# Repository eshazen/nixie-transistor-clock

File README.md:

In 2013 I built a clock from a kit purchased here:  https://tube-clock.com/

* [Manual](neon_man.pdf)

* set_board - start of a design to set the time using an ESP32
* case - acrylic case design

Some circuit analysis for setting remotely.

Set switches (ref schematic in manual):

SW1 (minutes) - page 8/23 (PDF page 70)
SW2 (Hours) - page 10/23 (PDF page 72)
SW3 (s hold) - page 2/23 (PDF page 64)

### 2026-05-11

Based on Peter's claim that WWVB reception was ok at Deb's place,
purchased a [Canaduino Atomic Clock](https://www.canaduino.ca/downloads/CANADUINO_Atomic_Clock_Receiver_Kit_V4.pdf)
board and 3D printed a little holder for it.  It seems to work OK
powered by 2xAA batteries in the kitchen.  Maybe at night it will work
in a window?

Per suggestion in the datasheet, thinking to connect with a shielded
RJ-45 patch cable.  Re-do `set_board_avr` to accommodate the connector,
and remove the 8MHz crystal and WiFi module.

Should probably add a couple of buttons.

Also, maybe need an additional small PCB for the WWVB board
with jumpers for LED and power (choose between battery and remote power).

### 2026-04-29

Confirm that ESP-01 works using FTDI at 115200 baud.
<br>Problem is that hardware UART on 8MHz AVR is unreliable.
<br>Downloaded https://github.com/nerdralph/picoUART
<br>Tested on "control panel" PCB with FTDI and seems to work

Starting to write some WiFi test code

### 2026-04-23

Reviving the "set board" project.  Thinking of a new design with an
ESP-01 serial WiFi module connected to a small AVR (ATTiny85?).
This could be much lower power or even fire up once only on power-up
to retrieve the time from somewhere.

The main issue may be poor wifi in the kitchen!

ESP-01 doco at:  https://nurdspace.nl/ESP8266

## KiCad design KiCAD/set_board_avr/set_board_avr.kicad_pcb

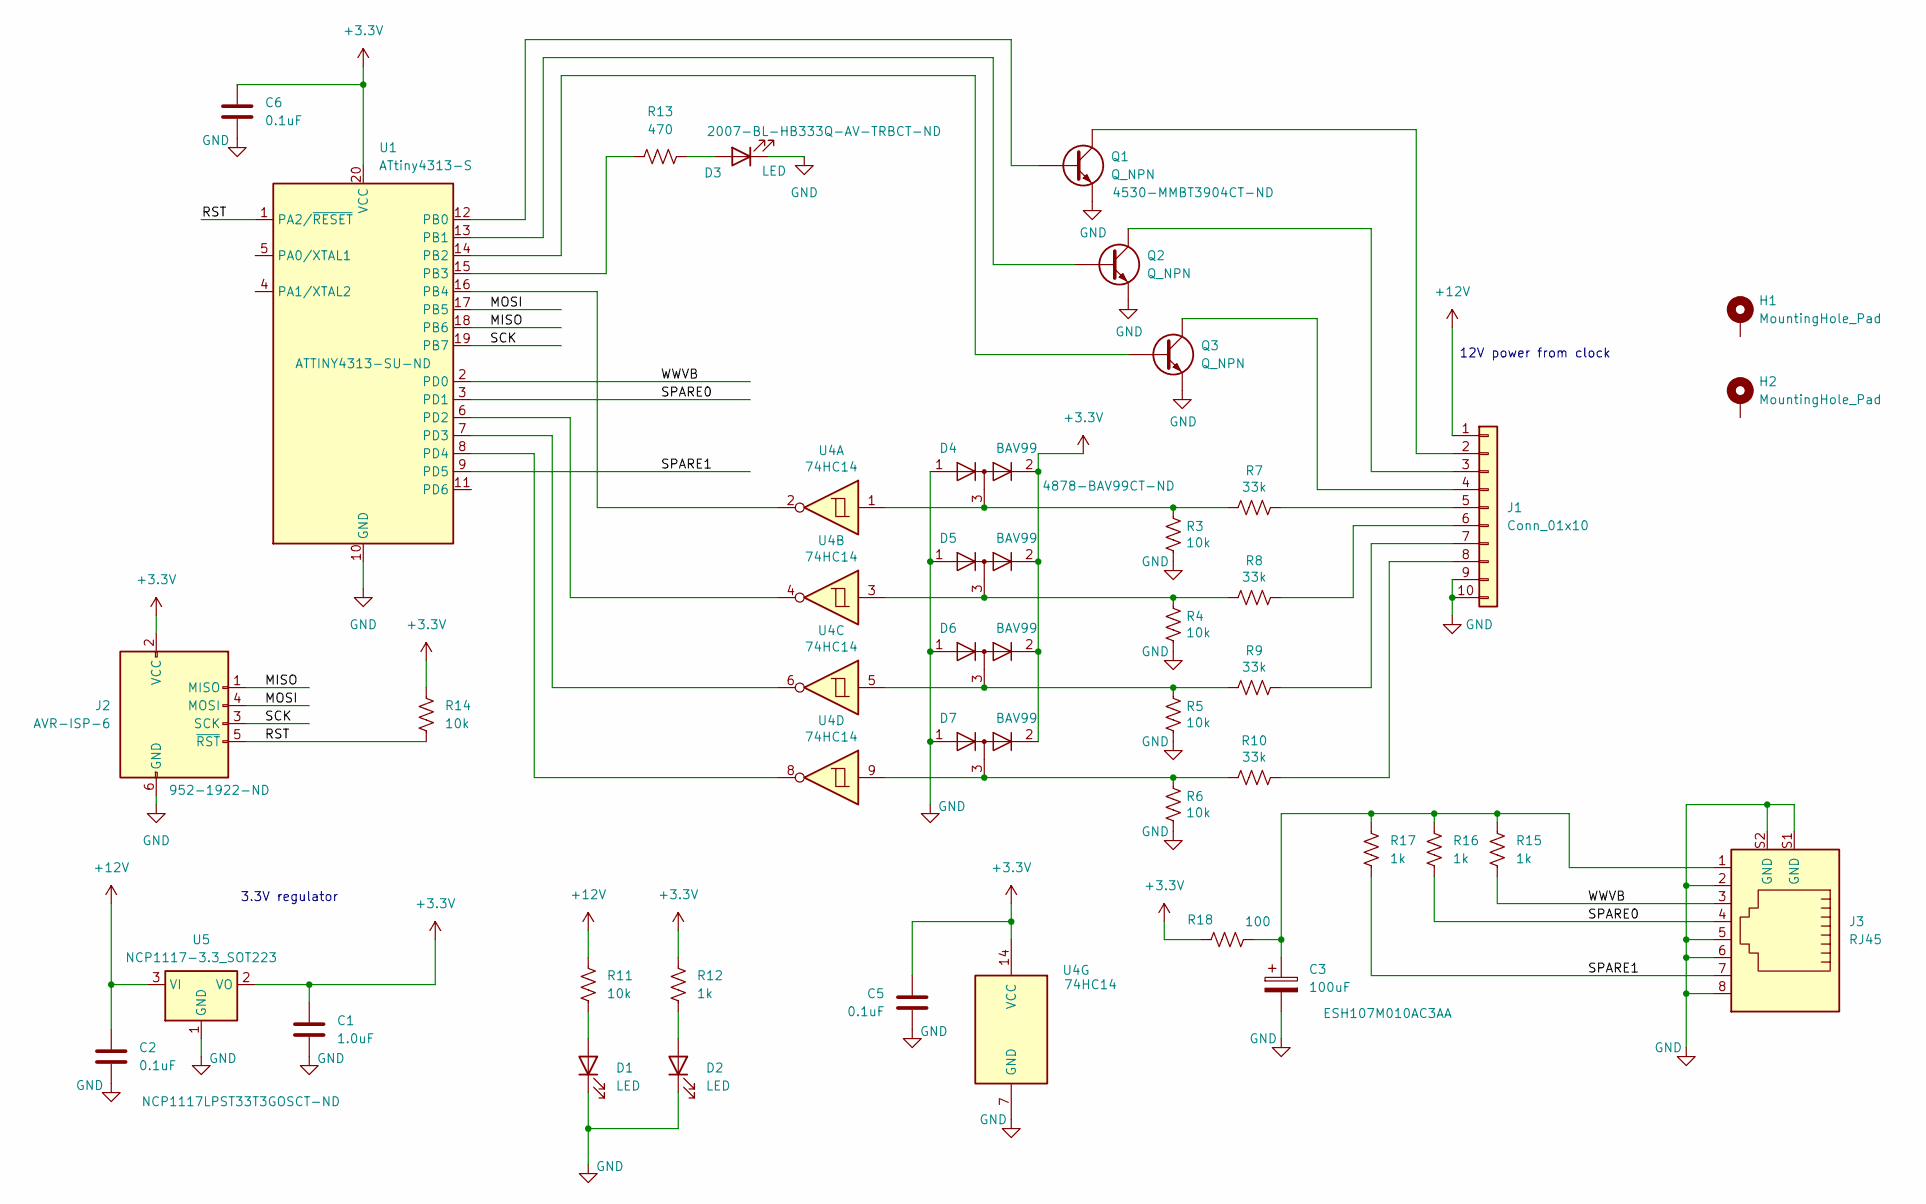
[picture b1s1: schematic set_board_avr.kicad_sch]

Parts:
C1: 1.0uF; C_1206_3216Metric_Pad1.33x1.80mm_HandSolder
C2, C5, C6: 0.1uF; C_1206_3216Metric_Pad1.33x1.80mm_HandSolder
C3: 100uF; CP_Radial_D5.0mm_P2.00mm
D1, D2, D3: LED; LED_1206_3216Metric
D4, D5, D6, D7: BAV99; SOT-23
H1, H2: MountingHole_Pad; MountingHole_4.5mm_Pad
J1: Conn_01x10; PinHeader_2x05_P2.54mm_Horizontal
J2: AVR-ISP-6; PinHeader_2x03_P2.54mm_Vertical_SMD
J3: RJ45; Metz_AJT65B8813
Q1, Q2, Q3: Q_NPN; SOT-23_Handsoldering_BEC
R3, R4, R5, R6, R11, R14: 10k; R_1206_3216Metric_Pad1.30x1.75mm_HandSolder
R7, R8, R9, R10: 33k; R_1206_3216Metric_Pad1.30x1.75mm_HandSolder
R12, R15, R16, R17: 1k; R_1206_3216Metric_Pad1.30x1.75mm_HandSolder
R13: 470; R_1206_3216Metric_Pad1.30x1.75mm_HandSolder
R18: 100; R_1206_3216Metric_Pad1.30x1.75mm_HandSolder
U1: ATtiny4313-S; SOIC-20W_7.5x12.8mm_P1.27mm
U4: 74HC14; SOIC-14_3.9x8.7mm_P1.27mm
U5: NCP1117-3.3_SOT223; SOT-223-3_TabPin2

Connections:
+3.3V: C1.1, C5.1, C6.1, D4.2 (A), D5.2 (A), D6.2 (A), D7.2 (A), J2.2 (VCC), R12.1, R14.1, R18.1, U1.20 (VCC), U4.14 (VCC), U5.2 (VO)
+12V: C2.1, J1.1, R11.1, U5.3 (VI)
/MISO: J2.1 (MISO), U1.18 (PB6)
/MOSI: J2.4 (MOSI), U1.17 (PB5)
/RST: J2.5 (~RST), R14.2, U1.1 (PA2/~RESET)
/SCK: J2.3 (SCK), U1.19 (PB7)
/SPARE0: J3.4, R16.2, U1.3 (PD1)
/SPARE1: J3.7, R17.2, U1.9 (PD5)
/WWVB: J3.3, R15.2, U1.2 (PD0)
GND: C1.2, C2.2, C3.2, C5.2, C6.2, D1.1 (K), D2.1 (K), D3.1 (K), D4.1 (K), D5.1 (K), D6.1 (K), D7.1 (K), J1.9, J1.10, J2.6 (GND), J3.2, J3.5, J3.6, J3.8, J3.S1 (GND), J3.S2 (GND), Q1.E, Q2.E, Q3.E, R3.2, R4.2, R5.2, R6.2, U1.10 (GND), U4.7 (GND), U5.1 (GND)
unnamed: C3.1, J3.1, R15.1, R16.1, R17.1, R18.2
unnamed: D1.2 (A), R11.2
unnamed: D2.2 (A), R12.2
unnamed: D3.2 (A), R13.2
unnamed: D4.3 (K), R3.1, R7.2, U4.1
unnamed: D5.3 (K), R4.1, R8.2, U4.3
unnamed: D6.3 (K), R5.1, R9.2, U4.5
unnamed: D7.3 (K), R6.1, R10.2, U4.9
unnamed: J1.2, Q1.C
unnamed: J1.3, Q2.C
unnamed: J1.4, Q3.C
unnamed: J1.5, R7.1
unnamed: J1.6, R8.1
unnamed: J1.7, R9.1
unnamed: J1.8, R10.1
unnamed: Q1.B, U1.12 (PB0)
unnamed: Q2.B, U1.13 (PB1)
unnamed: Q3.B, U1.14 (PB2)
unnamed: R13.1, U1.15 (PB3)
unnamed: U1.16 (PB4), U4.2
unnamed: U1.6 (PD2), U4.4
unnamed: U1.7 (PD3), U4.6
unnamed: U1.8 (PD4), U4.8

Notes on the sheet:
3.3V regulator
12V power from clock

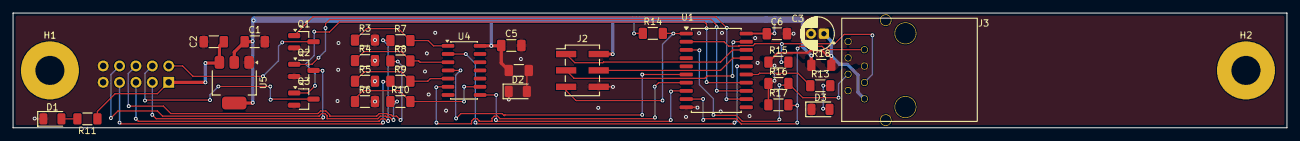
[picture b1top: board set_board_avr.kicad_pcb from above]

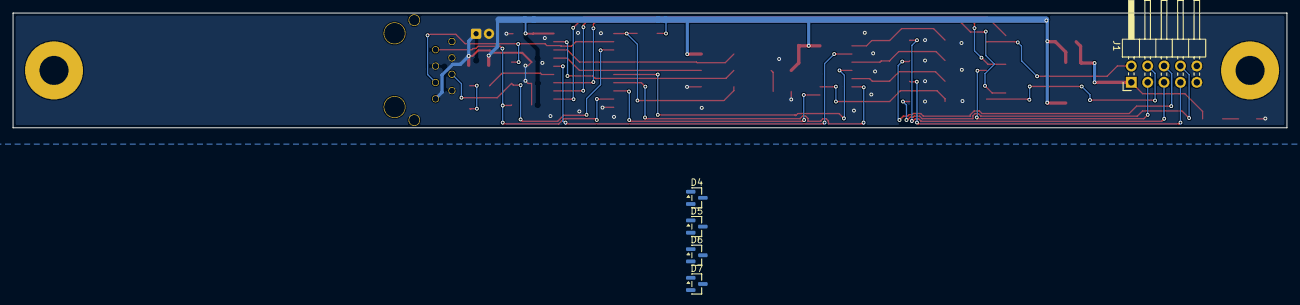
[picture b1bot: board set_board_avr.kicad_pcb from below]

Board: 2 copper layers, 197.5 x 17.8 mm, 39 parts (5 on the bottom side), 33 nets.

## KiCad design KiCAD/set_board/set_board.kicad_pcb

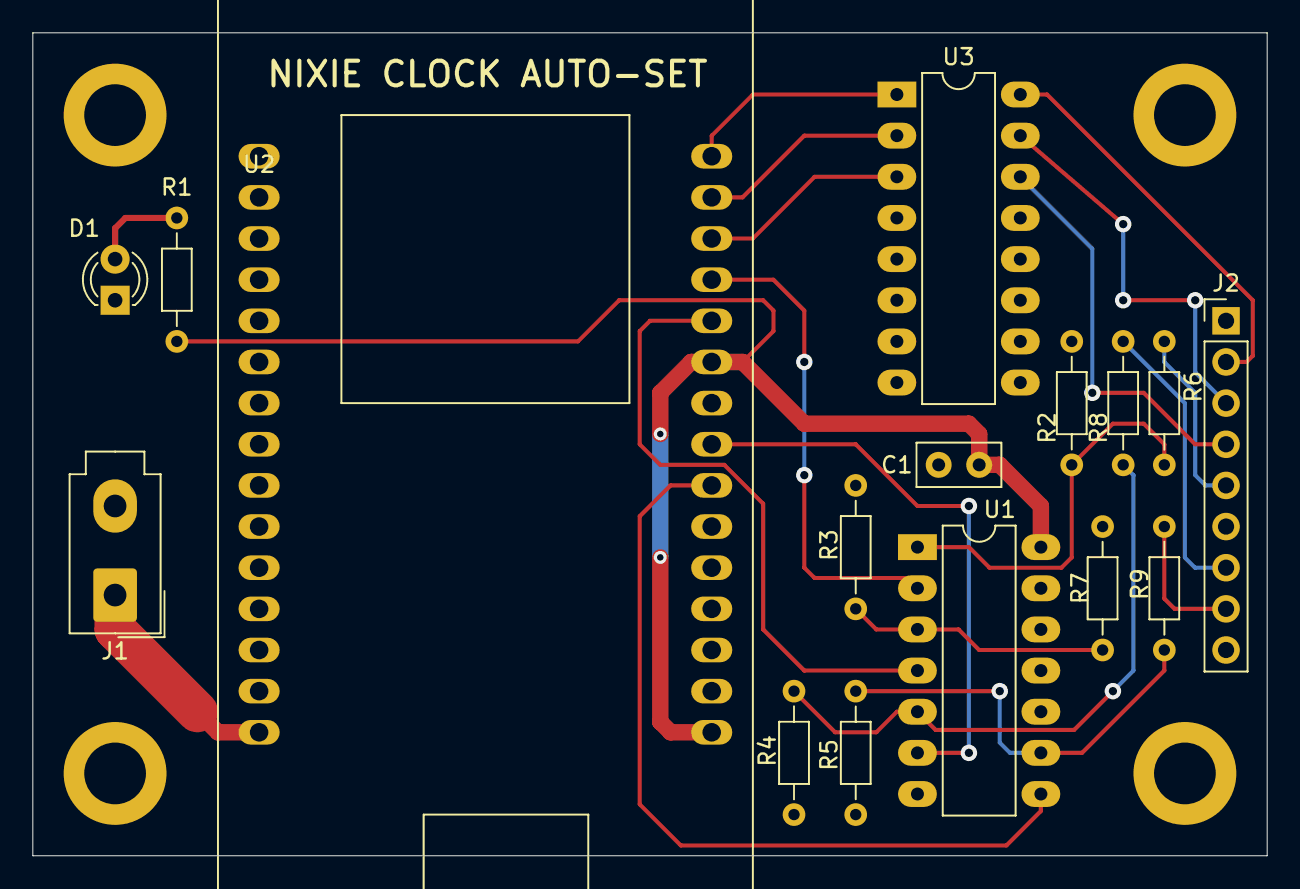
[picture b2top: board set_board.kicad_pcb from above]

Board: 2 copper layers, 76.2 x 50.8 mm, 16 parts (0 on the bottom side), 22 nets.

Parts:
C1: 0.1uF; C_Disc_D5.0mm_W2.5mm_P2.50mm
D1: LED; LED_D3.0mm
J1: Conn_01x02_Female; Molex_Mini-Fit_Jr_5566-02A_2x01_P4.20mm_Vertical
J2: Conn_01x10; PinHeader_1x09_P2.54mm_Vertical
R1: 330; R_Axial_DIN0204_L3.6mm_D1.6mm_P7.62mm_Horizontal
R2, R3, R4, R5: 10k; R_Axial_DIN0204_L3.6mm_D1.6mm_P7.62mm_Horizontal
R6, R7, R8, R9: 33k; R_Axial_DIN0204_L3.6mm_D1.6mm_P7.62mm_Horizontal
U1: 74HC14; DIP-14_W7.62mm_LongPads
U2: EPS8266; dip_30
U3: 75468; DIP-16_W7.62mm_LongPads

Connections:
+3V3: C1.1, R1.1, U1.14, U2.16, U2.25
GND: C1.2, D1.1, J1.2, J2.1, J2.9, R2.2, R3.2, R4.2, R5.2, U1.7, U2.10, U2.14, U2.17, U2.24, U3.8
unnamed: D1.2, R1.2
unnamed: J1.1, U2.15
unnamed: J2.2, U3.16
unnamed: J2.3, U3.15
unnamed: J2.4, U3.14
unnamed: J2.5, R6.1
unnamed: J2.6, R7.1
unnamed: J2.7, R8.1
unnamed: J2.8, R9.1
unnamed: R2.1, R6.2, U1.1
unnamed: R3.1, R7.2, U1.3
unnamed: R4.1, R8.2, U1.5
unnamed: R5.1, R9.2, U1.9
unnamed: U1.2, U2.27
unnamed: U1.4, U2.26
unnamed: U1.6, U2.23
unnamed: U1.8, U2.22
unnamed: U2.28, U3.3
unnamed: U2.29, U3.2
unnamed: U2.30, U3.1

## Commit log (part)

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2024-09-27 initial upload from SVN
2024-09-27 initial box design
2024-09-27 README, initial case design
2024-10-08 switch output to FETs
2024-10-09 ready to cut?
2024-10-09 mounting holes
2026-04-23 some updates
2026-04-23 rearrange docs
2026-04-23 working on new set board
2026-04-24 working on routing
2026-04-26 routed
2026-05-01 start WWVB board
2026-05-11 update for WWVB
2026-05-11 start possible WWVB board, update README
2026-05-30 finish place/route on set_board_avr
